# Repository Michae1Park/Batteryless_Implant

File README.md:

# SeniorDesign
Our Senior Design Project to build a medical implant for Rats

Contributor:
Michael Park,
Corey Cormier,
Albert Marzullo,
Makeila Sorensen,
Anish Vaghasia,
Thomas Ermis

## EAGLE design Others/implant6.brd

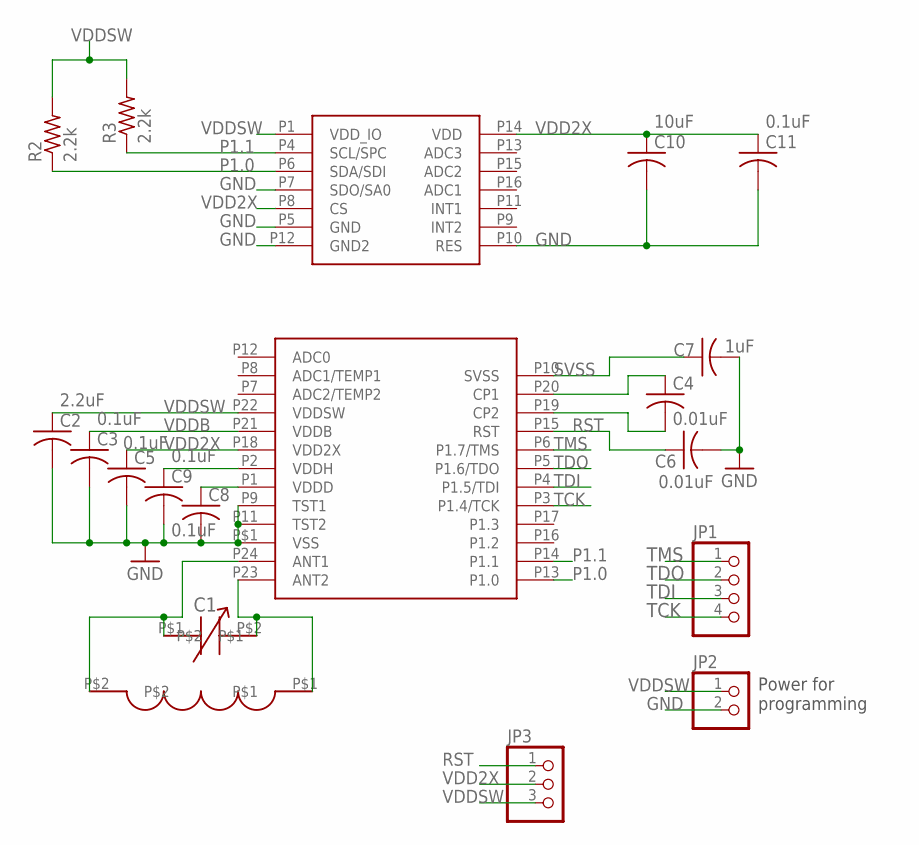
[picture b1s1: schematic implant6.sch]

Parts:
C2: 2.2uF; C0805
C3, C5, C8, C9, C11: 0.1uF; C0805
C4, C6: 0.01uF; C0805
C7: 1uF; C0805
C10: 10uF; C0805
JP1: PINHD-1X4; 1X04
JP2: PINHD-1X2; 1X02
JP3: PINHD-1X3; 1X03
R2, R3: 2.2k; R0805
U$1: RF430FRL152H; VQFN
U$2: COILCOIL3; COIL3
U$3: VAR_CAP
U$4: LIS3DH; LGA-16

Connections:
GND: C2.2, C3.2, C5.2, C6.2, C7.2, C8.2, C9.2, C10.2, C11.2, JP2.2, U$1.P9 (TST1), U$1.P11 (TST2), U$1.P$1 (VSS), U$4.P5 (GND), U$4.P7 (SDO/SA0), U$4.P10 (RES), U$4.P12 (GND2)
unnamed: C9.1, U$1.P2 (VDDH)
unnamed: C8.1, U$1.P1 (VDDD)
unnamed: U$1.P23 (ANT2), U$2.P$1, U$3.P$2
unnamed: C4.1, U$1.P20 (CP1)
unnamed: C4.2, U$1.P19 (CP2)
unnamed: U$1.P24 (ANT1), U$2.P$2, U$3.P$1
P1.0: R2.1, U$1.P13 (P1.0), U$4.P6 (SDA/SDI)
P1.1: R3.1, U$1.P14 (P1.1), U$4.P4 (SCL/SPC)
RST: C6.1, JP3.1, U$1.P15 (RST)
SVSS: C7.1, U$1.P10 (SVSS)
TCK: JP1.4, U$1.P3 (P1.4/TCK)
TDI: JP1.3, U$1.P4 (P1.5/TDI)
TDO: JP1.2, U$1.P5 (P1.6/TDO)
TMS: JP1.1, U$1.P6 (P1.7/TMS)
VDD2X: C5.1, C10.1, C11.1, JP3.2, U$1.P18 (VDD2X), U$4.P8 (CS), U$4.P14 (VDD)
VDDB: C3.1, U$1.P21 (VDDB)
VDDSW: C2.1, JP2.1, JP3.3, R2.2, R3.2, U$1.P22 (VDDSW), U$4.P1 (VDD_IO)

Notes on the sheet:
Power for programming

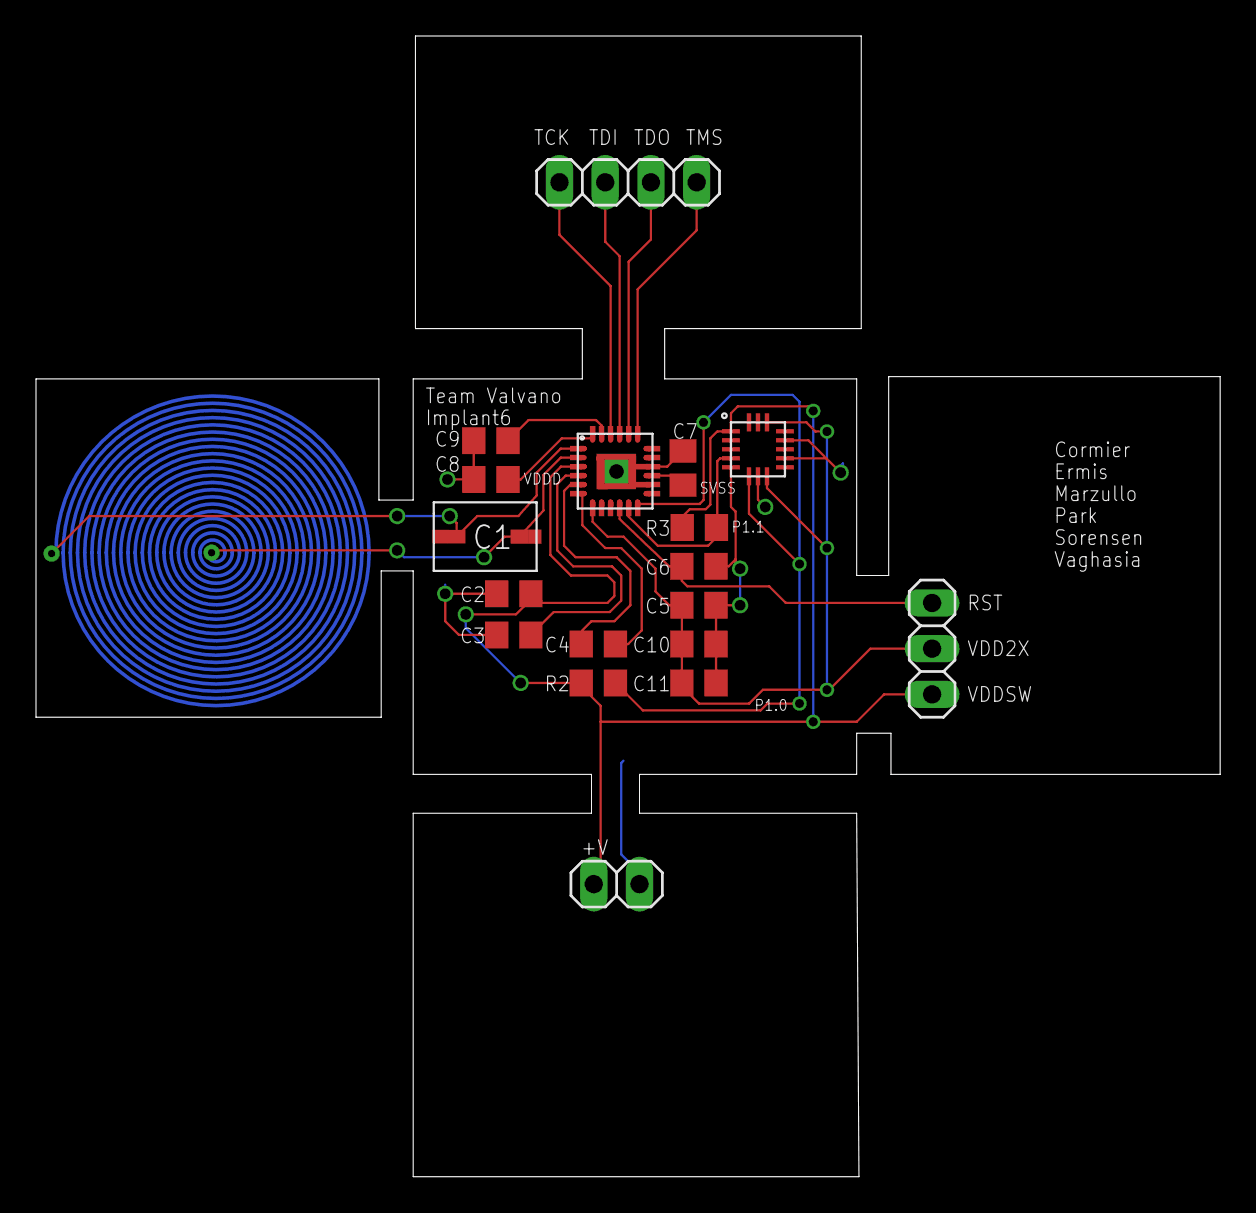
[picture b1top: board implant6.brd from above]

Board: 2 copper layers, 65.8 x 63.4 mm, 19 parts (1 on the bottom side), 18 nets.

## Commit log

2016-06-23 migrating repo from bitbucket
2016-06-23 TRF Control tested on Odroid XU$
2016-06-23 modified readme
2016-07-01 Added error message to InitSerial for Linux version
2016-07-24 Python script by Mak (and not Corey and Mike)
2016-08-26 stuff
2016-08-27 I2c master and slave - implant and accelerometer
2016-08-27 master folder
2016-08-29 Fix I2C communication
2016-08-30 test code for I2C tm4c123 as a slave - Working!
2016-09-02 minor change in TM4c
2017-07-11 Add files via upload
    keeping documents
2017-07-27 Add files via upload
    boards
